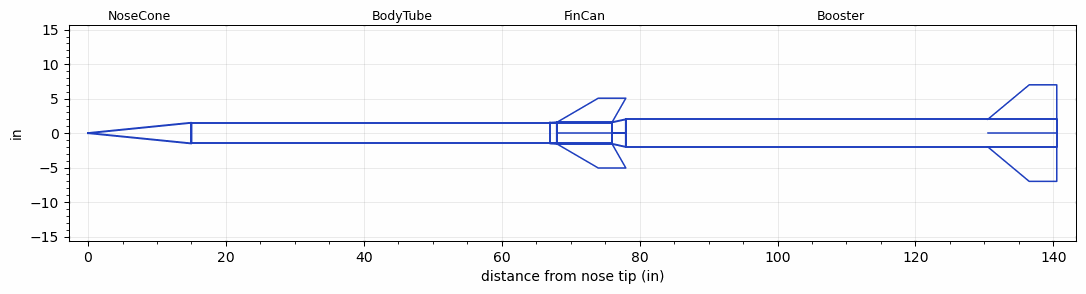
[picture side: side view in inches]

<RASAeroDocument>
 <FileVersion>2</FileVersion>
 <RocketDesign>
  <NoseCone>
   <Length>15</Length>
   <Diameter>3</Diameter>
   <Shape>Conical</Shape>
   <BluntRadius>0.0625</BluntRadius>
   <Location>0</Location>
  </NoseCone>
  <BodyTube>
   <Length>61</Length>
   <Diameter>3</Diameter>
   <Location>15</Location>
   <Protuberance>
    <StreamlinedNoBaseDrag>0</StreamlinedNoBaseDrag>
    <StreamlinedWithBaseDrag>0.4</StreamlinedWithBaseDrag>
    <InclinedPlate1Angle>0</InclinedPlate1Angle>
    <InclinedPlate1FrontalArea>0</InclinedPlate1FrontalArea>
    <InclinedPlate2Angle>0</InclinedPlate2Angle>
    <InclinedPlate2FrontalArea>0</InclinedPlate2FrontalArea>
   </Protuberance>
  </BodyTube>
  <FinCan>
   <Length>8</Length>
   <Diameter>3.125</Diameter>
   <InsideDiameter>3</InsideDiameter>
   <Location>76</Location>
   <ShoulderLength>1</ShoulderLength>
   <Offset>-8</Offset>
   <Fin>
    <Count>4</Count>
    <Chord>8</Chord>
    <Span>3.5</Span>
    <SweepDistance>6</SweepDistance>
    <TipChord>4</TipChord>
    <Thickness>0.15</Thickness>
    <LERadius>0.01</LERadius>
    <Location>8</Location>
    <AirfoilSection>Hexagonal</AirfoilSection>
    <FX1>1.5</FX1>
    <FX3>1.5</FX3>
   </Fin>
  </FinCan>
  <Booster>
   <Length>62.5</Length>
   <Diameter>4</Diameter>
   <InsideDiameter>3.125</InsideDiameter>
   <RailGuideDiameter>0.625</RailGuideDiameter>
   <RailGuideHeight>0.75</RailGuideHeight>
   <Location>76</Location>
   <ShoulderLength>2</ShoulderLength>
   <Fin>
    <Count>4</Count>
    <Chord>10</Chord>
    <Span>5</Span>
    <SweepDistance>6</SweepDistance>
    <TipChord>4</TipChord>
    <Thickness>0.15</Thickness>
    <LERadius>0.01</LERadius>
    <Location>10</Location>
    <AirfoilSection>Hexagonal</AirfoilSection>
    <FX1>1</FX1>
    <FX3>1</FX3>
   </Fin>
   <Protuberance>
    <StreamlinedNoBaseDrag>0</StreamlinedNoBaseDrag>
    <StreamlinedWithBaseDrag>0</StreamlinedWithBaseDrag>
    <InclinedPlate1Angle>20</InclinedPlate1Angle>
    <InclinedPlate1FrontalArea>0.5</InclinedPlate1FrontalArea>
    <InclinedPlate2Angle>0</InclinedPlate2Angle>
    <InclinedPlate2FrontalArea>0</InclinedPlate2FrontalArea>
   </Protuberance>
  </Booster>
  <Surface>Rough Camouflage Paint</Surface>
  <ModifiedBarrowman>True</ModifiedBarrowman>
  <Turbulence>True</Turbulence>
  <UseBooster1>False</UseBooster1>
  <UseBooster2>False</UseBooster2>
 </RocketDesign>
 <LaunchSite>
  <Altitude>3700</Altitude>
  <Pressure>0</Pressure>
  <RodAngle>5</RodAngle>
  <RodLength>20</RodLength>
  <Temperature>80</Temperature>
  <WindSpeed>5</WindSpeed>
 </LaunchSite>
 <Recovery>
  <Altitude1>1000</Altitude1>
  <Altitude2>3000</Altitude2>
  <DeviceType1>Parachute</DeviceType1>
  <DeviceType2>Parachute</DeviceType2>
  <Event1>True</Event1>
  <Event2>True</Event2>
  <Size1>9</Size1>
  <Size2>36</Size2>
  <EventType1>Apogee</EventType1>
  <EventType2>Altitude</EventType2>
  <CD1>1</CD1>
  <CD2>1.5</CD2>
 </Recovery>
 <SimulationList>
  <Simulation>
   <SustainerEngine>N4062  (TsKrush)</SustainerEngine>
   <SustainerLaunchWt>25.7</SustainerLaunchWt>
   <SustainerNozzleDiameter>2.5</SustainerNozzleDiameter>
   <SustainerCG>47.38</SustainerCG>
   <SustainerIgnitionDelay>10</SustainerIgnitionDelay>
   <Booster1Engine>O7548  (TsKrush)</Booster1Engine>
   <Booster1LaunchWt>68.7</Booster1LaunchWt>
   <Booster1SeparationDelay>0</Booster1SeparationDelay>
   <Booster1IgnitionDelay>0</Booster1IgnitionDelay>
   <Booster1CG>83.53</Booster1CG>
   <Booster1NozzleDiameter>3.5</Booster1NozzleDiameter>
   <IncludeBooster1>True</IncludeBooster1>
   <Booster2Delay>0</Booster2Delay>
   <IncludeBooster2>False</IncludeBooster2>
   <TimetoApogee>155.9553</TimetoApogee>
   <MaxAltitude>352151.9</MaxAltitude>
   <MaxVelocity>5565.996</MaxVelocity>
  </Simulation>
 </SimulationList>
</RASAeroDocument>
